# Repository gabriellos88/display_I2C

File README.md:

# display I2C OLED 128x64

Progetto per comandare un display OLED SSD1306 128x64 via I2C con il PIC18F45K22.

Il codice originale è stato preso da un post su [Forum MikroE](https://forum.mikroe.com/viewtopic.php?p=310697)
ed è stato ristrutturato con solo le funzioni necessarie e suddiviso con HAL.

Inoltre in [Hardware](Hardware/OLED_mikrobus_adapter) ho aggiunto la V1.0 dell' adattatore tra il 
mikro bus del PIC e il display (con supporti M3, TP e selezione VDD a 5V/3.3V).

## Struttura
...

## Funzioni principali

```c
display_clear();
display_pixel(10, 5, DISPLAY_COLOR_ON);
display_pixel(10, 5, DISPLAY_COLOR_OFF);
display_pixel(10, 5, DISPLAY_COLOR_INVERT);
display_line(0, 0, 127, 31, DISPLAY_COLOR_ON);
display_rect(0, 0, 128, 32, DISPLAY_COLOR_ON);
display_update();
```
Attenzione: il display viene aggiornato SOLO quando si chiama `display_update()`.

All'inizio il codice disegna un bordo, due diagonali e una griglia di pixel.

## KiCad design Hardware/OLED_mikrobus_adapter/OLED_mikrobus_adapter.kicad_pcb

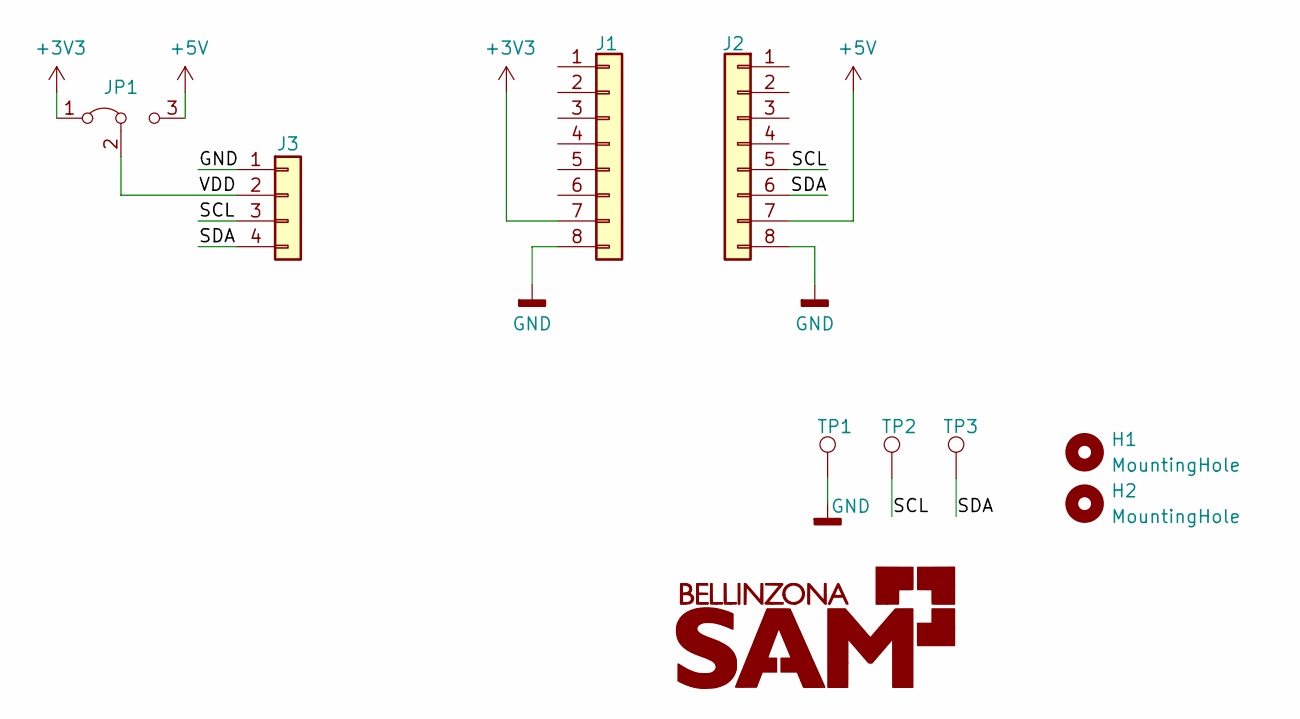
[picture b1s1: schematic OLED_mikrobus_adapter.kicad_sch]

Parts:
H1, H2: MountingHole; MountingHole_3.2mm_M3
J1, J2: Conn_01x08; PinHeader_1x08_P2.54mm_Vertical
J3: Conn_01x04; PinSocket_1x04_P2.54mm_Vertical
JP1: Jumper_3_Bridged12; PinHeader_1x03_P2.54mm_Vertical
TP1, TP2, TP3: TestPoint; Pin_D1.0mm_L10.0mm_LooseFit

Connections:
+3V3: J1.7, JP1.1 (A)
+5V: J2.7, JP1.3 (B)
/SCL: J2.5, J3.3, TP2.1
/SDA: J2.6, J3.4, TP3.1
/VDD: J3.2, JP1.2 (C)
GND: J1.8, J2.8, J3.1, TP1.1

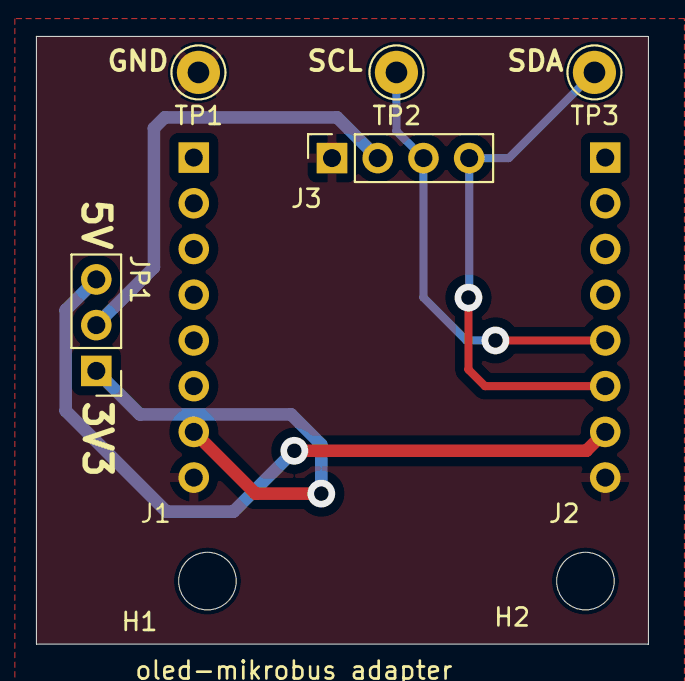
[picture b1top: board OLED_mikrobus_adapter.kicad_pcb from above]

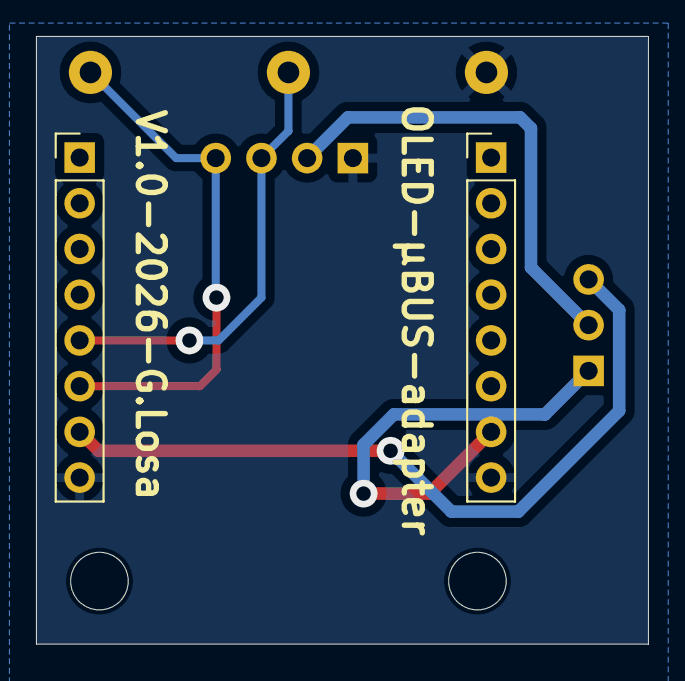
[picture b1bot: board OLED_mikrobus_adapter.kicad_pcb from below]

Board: 2 copper layers, 34.0 x 33.8 mm, 9 parts (2 on the bottom side), 6 nets.

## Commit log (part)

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2026-05-22 Restructured original software and added first hardware version (mikrobus-display adapter).
2026-05-22 Update README with formatted forum link
2026-05-22 Revise README for display I2C OLED project
    Updated README to improve clarity and added hardware adapter details.
2026-05-22 Improve README.md content and formatting
    Updated README.md for clarity and added details about the hardware adapter.
